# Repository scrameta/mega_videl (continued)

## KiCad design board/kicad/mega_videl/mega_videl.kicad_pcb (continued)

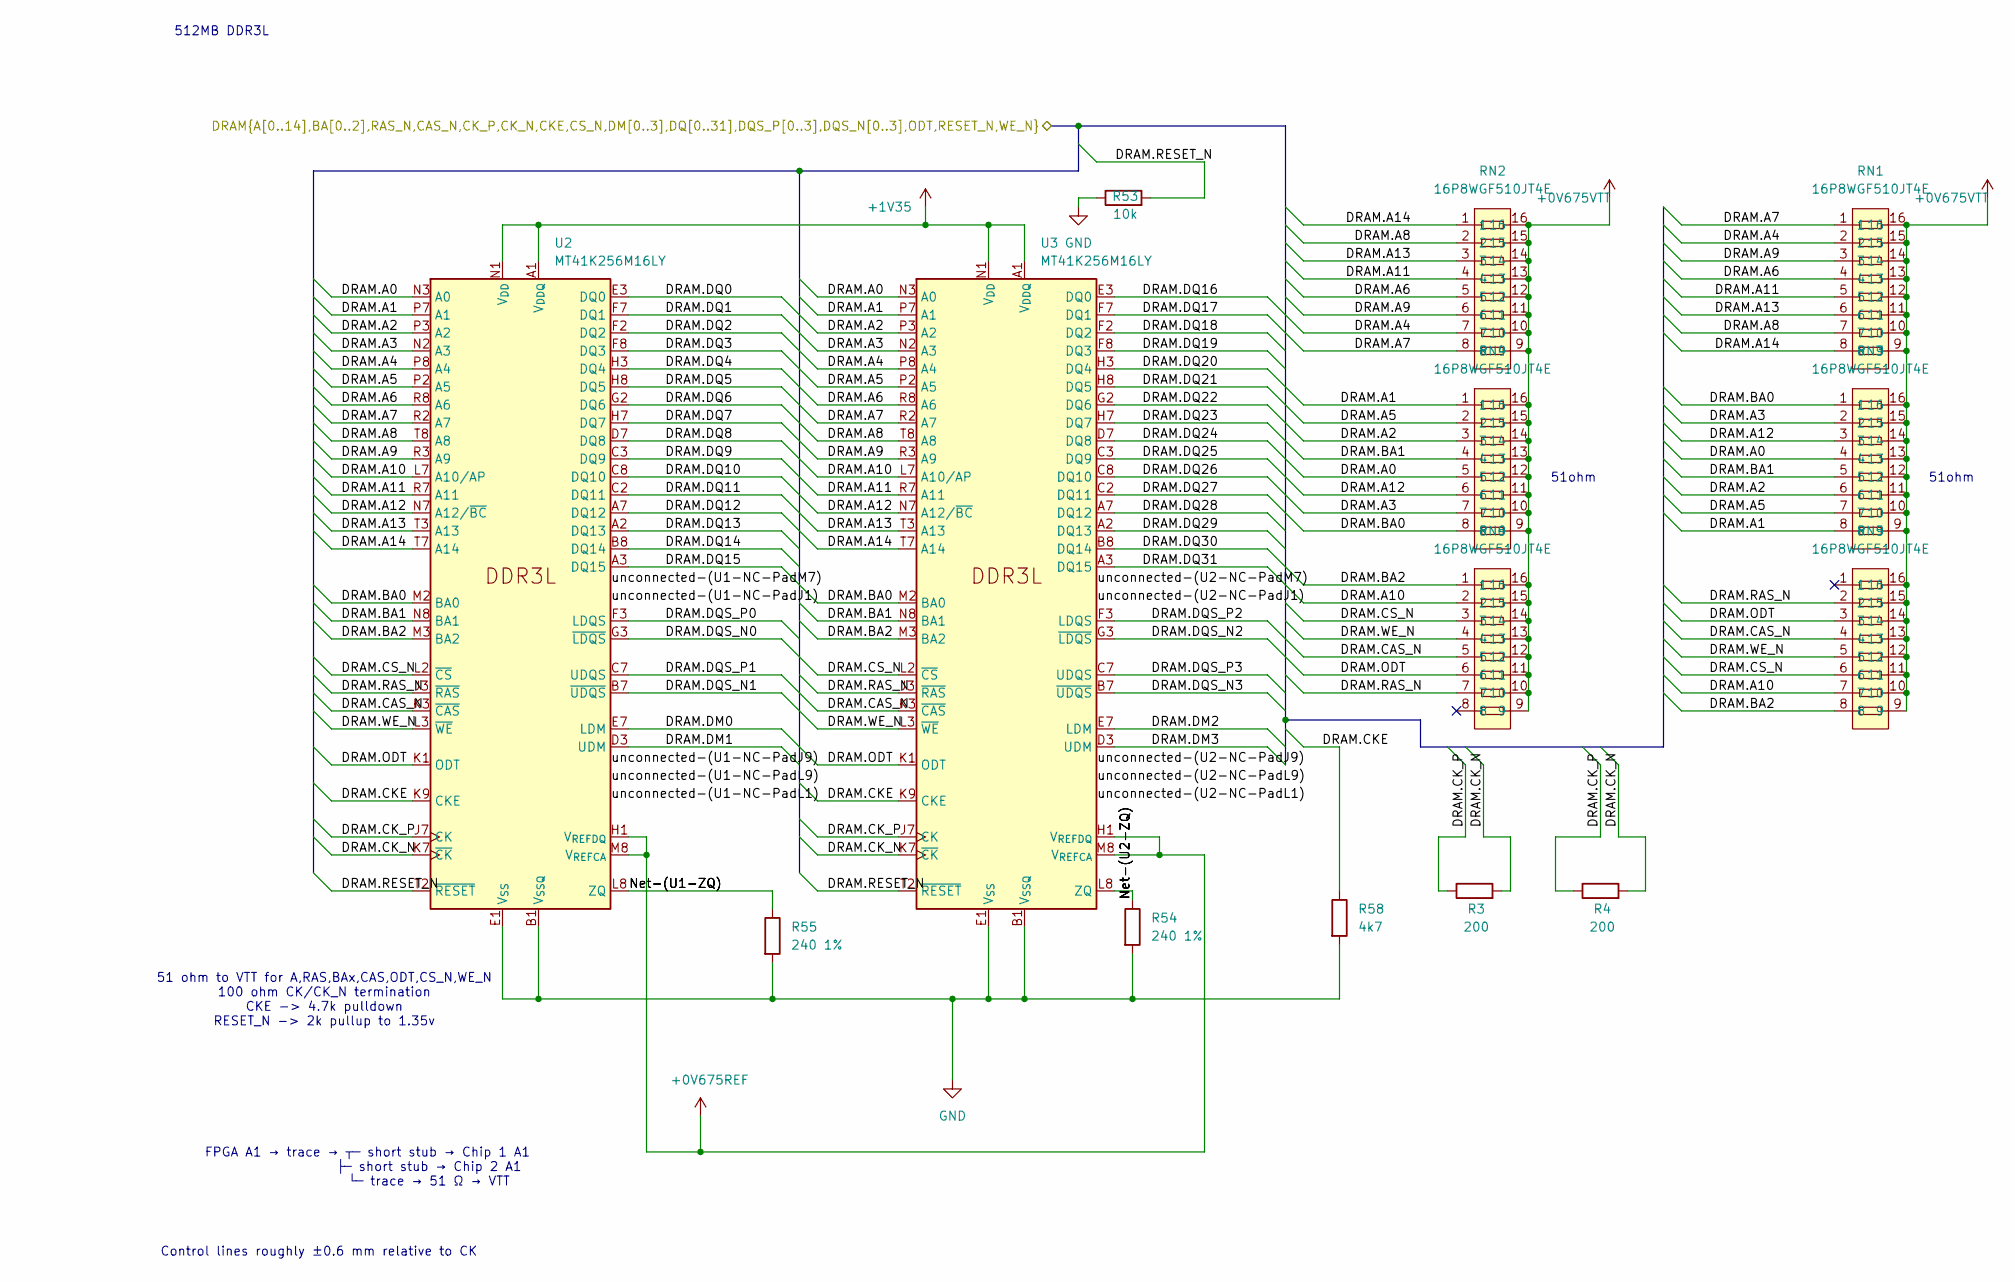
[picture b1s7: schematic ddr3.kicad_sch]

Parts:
R3, R4: 200; R_0402_1005Metric; LCSC C25087
R53: 10k; R_0603_1608Metric; LCSC C25804
R54, R55: 240 1%; R_0603_1608Metric; LCSC C23350
R58: 4k7; R_0603_1608Metric; LCSC C23162
RN1, RN2, RN3, RN4, RN5, RN6: 16P8WGF510JT4E; RES-ARRAY-SMD_0402-16P-L4.0-W1.6-BL-1; MPN 16P8WGF510JT4E; LCSC Part C422180
U2, U3: MT41K256M16LY; FBGA-96_L13.5-W7.5-P0.80-TL_MT41J256M16LY-091G; LCSC Part C253882

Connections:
+0V675REF: U2.H1 (V_{REFDQ}), U2.M8 (V_{REFCA}), U3.H1 (V_{REFDQ}), U3.M8 (V_{REFCA}); also elsewhere on the board
+0V675VTT: RN1.9, RN1.10, RN1.11, RN1.12, RN1.13, RN1.14, RN1.15, RN1.16, RN2.9, RN2.10, RN2.11, RN2.12, RN2.13, RN2.14, RN2.15, RN2.16, RN3.9, RN3.10, RN3.11, RN3.12, RN3.13, RN3.14, RN3.15, RN3.16, RN4.9, RN4.10, RN4.11, RN4.12, RN4.13, RN4.14, RN4.15, RN4.16, RN5.9, RN5.10, RN5.11, RN5.12, RN5.13, RN5.14, RN5.15, RN5.16, RN6.9, RN6.10, RN6.11, RN6.12, RN6.13, RN6.14, RN6.15, RN6.16; also elsewhere on the board
+1V35: U2.A1 (V_{DDQ}), U2.A8 (V_{DDQ}), U2.B2 (V_{DD}), U2.C1 (V_{DDQ}), U2.C9 (V_{DDQ}), U2.D2 (V_{DDQ}), U2.D9 (V_{DD}), U2.E9 (V_{DDQ}), U2.F1 (V_{DDQ}), U2.G7 (V_{DD}), U2.H2 (V_{DDQ}), U2.H9 (V_{DDQ}), U2.K2 (V_{DD}), U2.K8 (V_{DD}), U2.N1 (V_{DD}), U2.N9 (V_{DD}), U2.R1 (V_{DD}), U2.R9 (V_{DD}), U3.A1 (V_{DDQ}), U3.A8 (V_{DDQ}), U3.B2 (V_{DD}), U3.C1 (V_{DDQ}), U3.C9 (V_{DDQ}), U3.D2 (V_{DDQ}), U3.D9 (V_{DD}), U3.E9 (V_{DDQ}), U3.F1 (V_{DDQ}), U3.G7 (V_{DD}), U3.H2 (V_{DDQ}), U3.H9 (V_{DDQ}), U3.K2 (V_{DD}), U3.K8 (V_{DD}), U3.N1 (V_{DD}), U3.N9 (V_{DD}), U3.R1 (V_{DD}), U3.R9 (V_{DD}); also elsewhere on the board
/ddr3/Net-(U1-ZQ): R55.1, U2.L8 (ZQ)
/ddr3/Net-(U2-ZQ): R54.1, U3.L8 (ZQ)
/fpga/DRAM.A0: RN3.4, RN4.5, U2.N3 (A0), U3.N3 (A0); also elsewhere on the board
/fpga/DRAM.A1: RN3.8, RN4.1, U2.P7 (A1), U3.P7 (A1); also elsewhere on the board
/fpga/DRAM.A2: RN3.6, RN4.3, U2.P3 (A2), U3.P3 (A2); also elsewhere on the board
/fpga/DRAM.A3: RN3.2, RN4.7, U2.N2 (A3), U3.N2 (A3); also elsewhere on the board
/fpga/DRAM.A4: RN1.2, RN2.7, U2.P8 (A4), U3.P8 (A4); also elsewhere on the board
/fpga/DRAM.A5: RN3.7, RN4.2, U2.P2 (A5), U3.P2 (A5); also elsewhere on the board
/fpga/DRAM.A6: RN1.4, RN2.5, U2.R8 (A6), U3.R8 (A6); also elsewhere on the board
/fpga/DRAM.A7: RN1.1, RN2.8, U2.R2 (A7), U3.R2 (A7); also elsewhere on the board
/fpga/DRAM.A8: RN1.7, RN2.2, U2.T8 (A8), U3.T8 (A8); also elsewhere on the board
/fpga/DRAM.A9: RN1.3, RN2.6, U2.R3 (A9), U3.R3 (A9); also elsewhere on the board
/fpga/DRAM.A10: RN5.7, RN6.2, U2.L7 (A10/AP), U3.L7 (A10/AP); also elsewhere on the board
/fpga/DRAM.A11: RN1.5, RN2.4, U2.R7 (A11), U3.R7 (A11); also elsewhere on the board
/fpga/DRAM.A12: RN3.3, RN4.6, U2.N7 (A12/~BC), U3.N7 (A12/~BC); also elsewhere on the board
/fpga/DRAM.A13: RN1.6, RN2.3, U2.T3 (A13), U3.T3 (A13); also elsewhere on the board
/fpga/DRAM.A14: RN1.8, RN2.1, U2.T7 (A14), U3.T7 (A14); also elsewhere on the board
/fpga/DRAM.BA0: RN3.1, RN4.8, U2.M2 (BA0), U3.M2 (BA0); also elsewhere on the board
/fpga/DRAM.BA1: RN3.5, RN4.4, U2.N8 (BA1), U3.N8 (BA1); also elsewhere on the board
/fpga/DRAM.BA2: RN5.8, RN6.1, U2.M3 (BA2), U3.M3 (BA2); also elsewhere on the board
/fpga/DRAM.CAS_N: RN5.4, RN6.5, U2.K3 (~CAS), U3.K3 (~CAS); also elsewhere on the board
/fpga/DRAM.CKE: R58.1, U2.K9 (CKE), U3.K9 (CKE); also elsewhere on the board
/fpga/DRAM.CK_N: R3.2, R4.2, U2.K7 (~CK), U3.K7 (~CK); also elsewhere on the board
/fpga/DRAM.CK_P: R3.1, R4.1, U2.J7 (CK), U3.J7 (CK); also elsewhere on the board
/fpga/DRAM.CS_N: RN5.6, RN6.3, U2.L2 (~CS), U3.L2 (~CS); also elsewhere on the board
/fpga/DRAM.DM0: U2.E7 (LDM); also elsewhere on the board
/fpga/DRAM.DM1: U2.D3 (UDM); also elsewhere on the board
/fpga/DRAM.DM2: U3.E7 (LDM); also elsewhere on the board
/fpga/DRAM.DM3: U3.D3 (UDM); also elsewhere on the board
/fpga/DRAM.DQ0: U2.E3 (DQ0); also elsewhere on the board
/fpga/DRAM.DQ1: U2.F7 (DQ1); also elsewhere on the board
/fpga/DRAM.DQ2: U2.F2 (DQ2); also elsewhere on the board
/fpga/DRAM.DQ3: U2.F8 (DQ3); also elsewhere on the board
/fpga/DRAM.DQ4: U2.H3 (DQ4); also elsewhere on the board
/fpga/DRAM.DQ5: U2.H8 (DQ5); also elsewhere on the board
/fpga/DRAM.DQ6: U2.G2 (DQ6); also elsewhere on the board
/fpga/DRAM.DQ7: U2.H7 (DQ7); also elsewhere on the board
/fpga/DRAM.DQ8: U2.D7 (DQ8); also elsewhere on the board
/fpga/DRAM.DQ9: U2.C3 (DQ9); also elsewhere on the board
/fpga/DRAM.DQ10: U2.C8 (DQ10); also elsewhere on the board
/fpga/DRAM.DQ11: U2.C2 (DQ11); also elsewhere on the board
/fpga/DRAM.DQ12: U2.A7 (DQ12); also elsewhere on the board
/fpga/DRAM.DQ13: U2.A2 (DQ13); also elsewhere on the board
/fpga/DRAM.DQ14: U2.B8 (DQ14); also elsewhere on the board
/fpga/DRAM.DQ15: U2.A3 (DQ15); also elsewhere on the board
/fpga/DRAM.DQ16: U3.E3 (DQ0); also elsewhere on the board
/fpga/DRAM.DQ17: U3.F7 (DQ1); also elsewhere on the board
/fpga/DRAM.DQ18: U3.F2 (DQ2); also elsewhere on the board
/fpga/DRAM.DQ19: U3.F8 (DQ3); also elsewhere on the board
/fpga/DRAM.DQ20: U3.H3 (DQ4); also elsewhere on the board
/fpga/DRAM.DQ21: U3.H8 (DQ5); also elsewhere on the board
/fpga/DRAM.DQ22: U3.G2 (DQ6); also elsewhere on the board
/fpga/DRAM.DQ23: U3.H7 (DQ7); also elsewhere on the board
/fpga/DRAM.DQ24: U3.D7 (DQ8); also elsewhere on the board
/fpga/DRAM.DQ25: U3.C3 (DQ9); also elsewhere on the board
/fpga/DRAM.DQ26: U3.C8 (DQ10); also elsewhere on the board
/fpga/DRAM.DQ27: U3.C2 (DQ11); also elsewhere on the board
/fpga/DRAM.DQ28: U3.A7 (DQ12); also elsewhere on the board
/fpga/DRAM.DQ29: U3.A2 (DQ13); also elsewhere on the board
/fpga/DRAM.DQ30: U3.B8 (DQ14); also elsewhere on the board
/fpga/DRAM.DQ31: U3.A3 (DQ15); also elsewhere on the board
/fpga/DRAM.DQS_N0: U2.G3 (~LDQS); also elsewhere on the board
/fpga/DRAM.DQS_N1: U2.B7 (~UDQS); also elsewhere on the board
/fpga/DRAM.DQS_N2: U3.G3 (~LDQS); also elsewhere on the board
/fpga/DRAM.DQS_N3: U3.B7 (~UDQS); also elsewhere on the board
/fpga/DRAM.DQS_P0: U2.F3 (LDQS); also elsewhere on the board
/fpga/DRAM.DQS_P1: U2.C7 (UDQS); also elsewhere on the board
/fpga/DRAM.DQS_P2: U3.F3 (LDQS); also elsewhere on the board
/fpga/DRAM.DQS_P3: U3.C7 (UDQS); also elsewhere on the board
/fpga/DRAM.ODT: RN5.3, RN6.6, U2.K1 (ODT), U3.K1 (ODT); also elsewhere on the board
/fpga/DRAM.RAS_N: RN5.2, RN6.7, U2.J3 (~RAS), U3.J3 (~RAS); also elsewhere on the board
/fpga/DRAM.RESET_N: R53.2, U2.T2 (~RESET), U3.T2 (~RESET); also elsewhere on the board
/fpga/DRAM.WE_N: RN5.5, RN6.4, U2.L3 (~WE), U3.L3 (~WE); also elsewhere on the board
GND: R53.1, R54.2, R55.2, R58.2, U2.A9 (V_{SS}), U2.B1 (V_{SSQ}), U2.B3 (V_{SS}), U2.B9 (V_{SSQ}), U2.D1 (V_{SSQ}), U2.D8 (V_{SSQ}), U2.E1 (V_{SS}), U2.E2 (V_{SSQ}), U2.E8 (V_{SSQ}), U2.F9 (V_{SSQ}), U2.G1 (V_{SSQ}), U2.G8 (V_{SS}), U2.G9 (V_{SSQ}), U2.J2 (V_{SS}), U2.J8 (V_{SS}), U2.M1 (V_{SS}), U2.M9 (V_{SS}), U2.P1 (V_{SS}), U2.P9 (V_{SS}), U2.T1 (V_{SS}), U2.T9 (V_{SS}), U3.A9 (V_{SS}), U3.B1 (V_{SSQ}), U3.B3 (V_{SS}), U3.B9 (V_{SSQ}), U3.D1 (V_{SSQ}), U3.D8 (V_{SSQ}), U3.E1 (V_{SS}), U3.E2 (V_{SSQ}), U3.E8 (V_{SSQ}), U3.F9 (V_{SSQ}), U3.G1 (V_{SSQ}), U3.G8 (V_{SS}), U3.G9 (V_{SSQ}), U3.J2 (V_{SS}), U3.J8 (V_{SS}), U3.M1 (V_{SS}), U3.M9 (V_{SS}), U3.P1 (V_{SS}), U3.P9 (V_{SS}), U3.T1 (V_{SS}), U3.T9 (V_{SS}); also elsewhere on the board

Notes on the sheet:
51ohm
512MB DDR3L
Control lines roughly ±0.6 mm relative to CK
FPGA A1 → trace → ┬─ short stub → Chip 1 A1 ├─ short stub → Chip 2 A1 └─ trace → 51 Ω → VTT
51 ohm to VTT for A,RAS,BAx,CAS,ODT,CS_N,WE_N 100 ohm CK/CK_N termination CKE -> 4.7k pulldown RESET_N -> 2k pullup to 1.35v

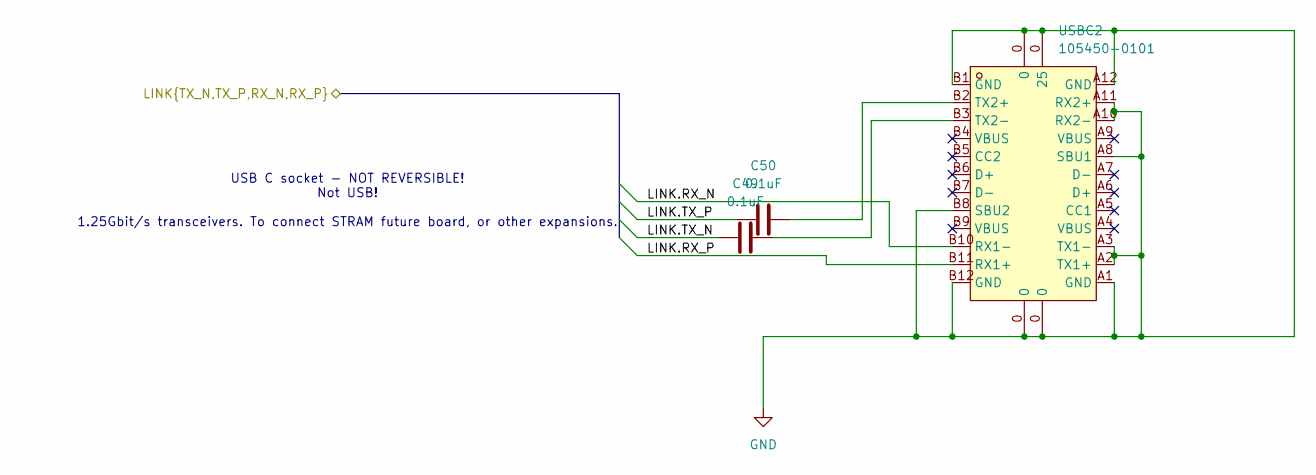
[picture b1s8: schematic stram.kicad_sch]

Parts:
C49, C50: 0.1uF; C_0603_1608Metric; LCSC C14663
USBC2: 105450-0101; USB-C-SMD_TYPE-C-USB-18; MPN 1054500101; LCSC Part C134092

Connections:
/fpga/LINK.RX_N: USBC2.B10 (RX1-); also elsewhere on the board
/fpga/LINK.RX_P: USBC2.B11 (RX1+); also elsewhere on the board
/fpga/LINK.TX_N: C49.1; also elsewhere on the board
/fpga/LINK.TX_P: C50.1; also elsewhere on the board
GND: USBC2.0, USBC2.A1 (GND), USBC2.A2 (TX1+), USBC2.A3 (TX1-), USBC2.A8 (SBU1), USBC2.A10 (RX2-), USBC2.A11 (RX2+), USBC2.A12 (GND), USBC2.B1 (GND), USBC2.B8 (SBU2), USBC2.B12 (GND); also elsewhere on the board
unnamed: C50.2, USBC2.B2 (TX2+)
unnamed: C49.2, USBC2.B3 (TX2-)

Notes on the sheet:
USB C socket - NOT REVERSIBLE! Not USB! 1.25Gbit/s transceivers. To connect STRAM future board, or other expansions.

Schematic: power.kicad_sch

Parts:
C13: 100uF; C_1206_3216Metric; LCSC C7432784
C16, C22: 10nF; C_0402_1005Metric; LCSC C15195
C19, C23, C25: 10uF; C_0805_2012Metric; LCSC C15850
C21, C24, C27: 22uF; C_0805_2012Metric; LCSC C45783
J2: Conn_01x04; PinHeader_1x04_P2.54mm_Vertical; not fitted
L1, L2: 1uF/DFE252012F-1R0M=P2; L_1008_2520Metric; LCSC C435392
R5: 11K0; R_0603_1608Metric; LCSC C25950
R6, R14: 32k4; R_0603_1608Metric; LCSC C13187
R7, R15: 10k; R_0603_1608Metric; LCSC C25804
R13: 16K9; R_0603_1608Metric; LCSC C25954
U4, U8: TPS62903RPJR; VQFN-HR-9_L2.0-W1.5-P0.50-TL; Manufacturer Part TPS62903RPJR; LCSC C2866502
U6: TPS7A2025PDBVR; SOT-23-5_L2.9-W1.6-P0.95-LS2.8-BR; MPN TPS7A2025PDBVR; LCSC Part C2869949

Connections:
+1V1: C21.1, J2.4, L1.1, U4.3 (VOS); also elsewhere on the board
+1V35: C27.1, J2.3, L2.1, U8.3 (VOS); also elsewhere on the board
+2V5: C24.1, U6.5 (OUT); also elsewhere on the board
+3V3: C13.1, C19.1, C23.1, C25.1, J2.2, R7.1, R15.1, U4.5 (EN), U4.6 (VIN), U6.1 (IN), U6.3 (EN), U8.5 (EN), U8.6 (VIN); also elsewhere on the board
/power/Net-(U15-FB/VSET): R5.1, U4.9 (FB/VSET)
/power/Net-(U15-MODE/S-CONF): R6.1, U4.7 (MODE/S-CONF)
/power/Net-(U15-PG): R7.2, U4.1 (PG)
/power/Net-(U15-SS/TR): C16.1, U4.8 (SS/TR)
/power/Net-(U15-SW): L1.2, U4.2 (SW)
/power/Net-(U16-FB/VSET): R13.1, U8.9 (FB/VSET)
/power/Net-(U16-MODE/S-CONF): R14.1, U8.7 (MODE/S-CONF)
/power/Net-(U16-PG): R15.2, U8.1 (PG)
/power/Net-(U16-SS/TR): C22.1, U8.8 (SS/TR)
/power/Net-(U16-SW): L2.2, U8.2 (SW)
/power/unconnected-(U8-N/C-Pad4): U6.4 (N/C)
GND: C13.2, C16.2, C19.2, C21.2, C22.2, C23.2, C24.2, C25.2, C27.2, J2.1, R5.2, R6.2, R13.2, R14.2, U4.4 (GND), U6.2 (GND), U8.4 (GND); also elsewhere on the board

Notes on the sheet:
3.3v in from CT60 2.5v LDO (small one from Pokeymax) 1.35v for DDR3L 1.1v for Cyclone VE
Cyclone V G unsequenced -> 1.1(CORE)->2.5(PLL)->1.35(IO) + 3.3 (IO)
MODE VSET 2.5MHz Discharge AUTO = 26.1k to GND VSET 2.5MHz Discharge PWM = 32.4k to GND
VSET 1.35V - 16.9K 1.1V - 11.0K

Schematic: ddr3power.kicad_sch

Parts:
C1, C60, C61: 0.1uF; C_0603_1608Metric; LCSC C14663
C2, C3, C5, C6, C7, C11, C12: 10uF; C_0805_2012Metric; LCSC C15850
C4, C51, C52, C53, C54, C73, C74, C75, C76: 4.7uF; C_0805_2012Metric; LCSC C1779
C8, C9, C14, C15, C17, C18: CA0612KRX7R7BB104; CAP-ARRAY-SMD_0612-8P-L3.2-W1.6-BL; MPN CA0612KRX7R7BB104; LCSC Part C576639
C10: 1nF; C_0603_1608Metric; LCSC C1588
C55, C56, C57, C58, C59, C62, C63, C64, C65, C66, C67, C68, C69, C70, C71, C72: 0.1uF; C_0402_1005Metric; LCSC C1525
R1, R2: 10k; R_0603_1608Metric; LCSC C25804
U1: TPS51200DRCR; WSON-10_L3.0-W3.0-P0.50-BL-EP; MPN TPS51200DRCR; LCSC Part C34771

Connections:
+0V675REF: C1.1, C60.1, C61.1, U1.6 (REFOUT); also elsewhere on the board
+0V675VTT: C2.1, C3.1, C5.1, C6.1, C7.1, C8.5, C8.6, C8.7, C8.8, C9.5, C9.6, C9.7, C9.8, C14.5, C14.6, C14.7, C14.8, C15.5, C15.6, C15.7, C15.8, C17.5, C17.6, C17.7, C17.8, C18.5, C18.6, C18.7, C18.8, U1.3 (VO), U1.5 (VOSNS); also elsewhere on the board
+1V35: C11.1, C12.1, C51.1, C52.1, C53.1, C54.1, C55.1, C56.1, C57.1, C58.1, C59.1, C62.1, C63.1, C64.1, C65.1, C66.1, C67.1, C68.1, C69.1, C70.1, C71.1, C72.1, C73.1, C74.1, C75.1, C76.1, R2.1, U1.2 (VLDOIN); also elsewhere on the board
+3V3: C4.1, U1.7 (EN), U1.10 (VIN); also elsewhere on the board
/ddr3power/Net-(U7-REFIN): C10.1, R1.1, R2.2, U1.1 (REFIN)
/ddr3power/unconnected-(U7-PGOOD-Pad9): U1.9 (PGOOD)
GND: C1.2, C2.2, C3.2, C4.2, C5.2, C6.2, C7.2, C8.1, C8.2, C8.3, C8.4, C9.1, C9.2, C9.3, C9.4, C10.2, C11.2, C12.2, C14.1, C14.2, C14.3, C14.4, C15.1, C15.2, C15.3, C15.4, C17.1, C17.2, C17.3, C17.4, C18.1, C18.2, C18.3, C18.4, C51.2, C52.2, C53.2, C54.2, C55.2, C56.2, C57.2, C58.2, C59.2, C60.2, C61.2, C62.2, C63.2, C64.2, C65.2, C66.2, C67.2, C68.2, C69.2, C70.2, C71.2, C72.2, C73.2, C74.2, C75.2, C76.2, R1.2, U1.4 (PGND), U1.8 (GND), U1.11 (EPAD); also elsewhere on the board

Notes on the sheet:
0.1uF

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
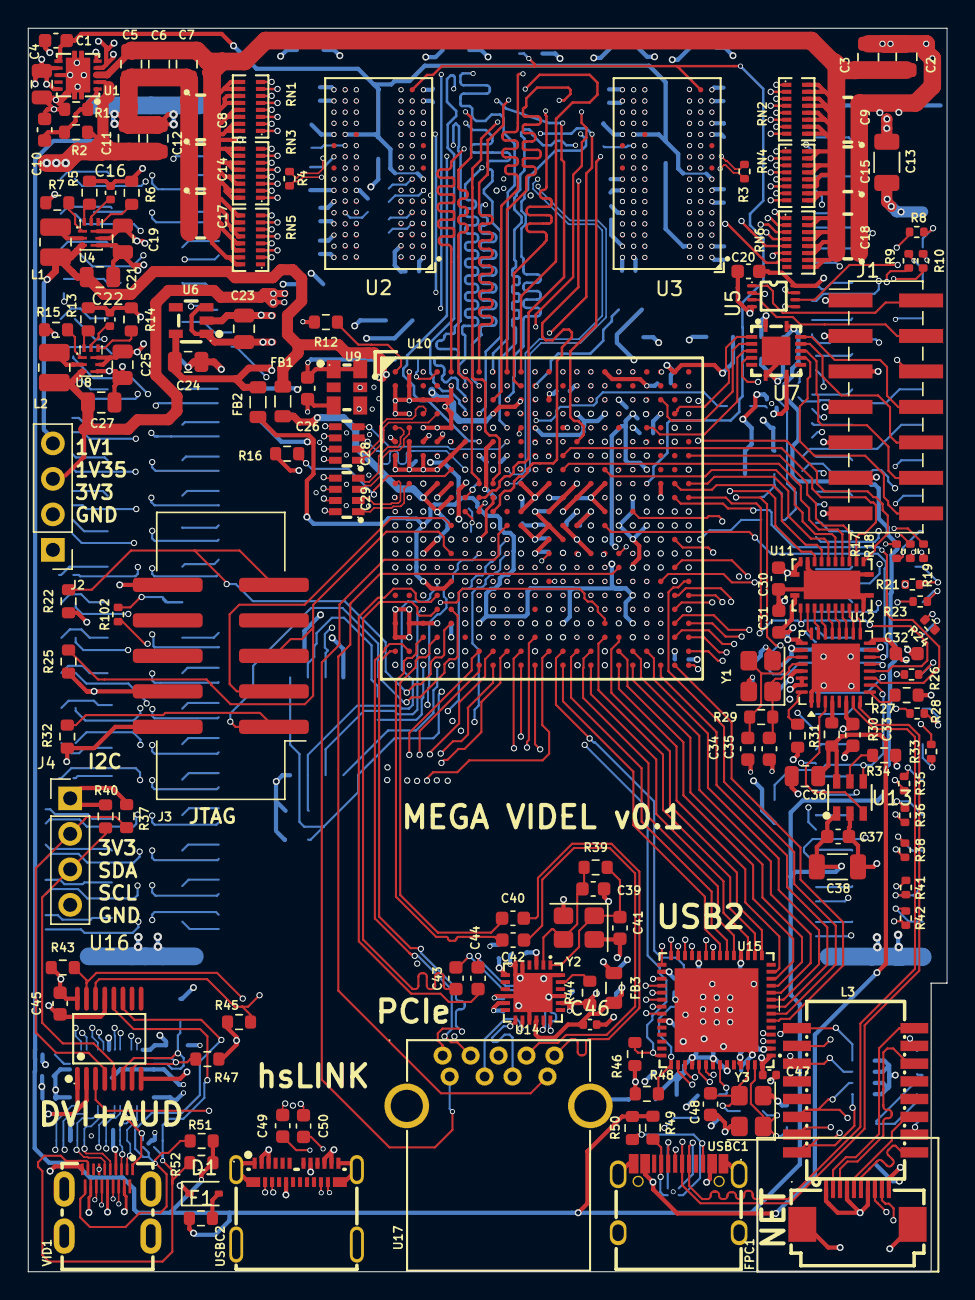
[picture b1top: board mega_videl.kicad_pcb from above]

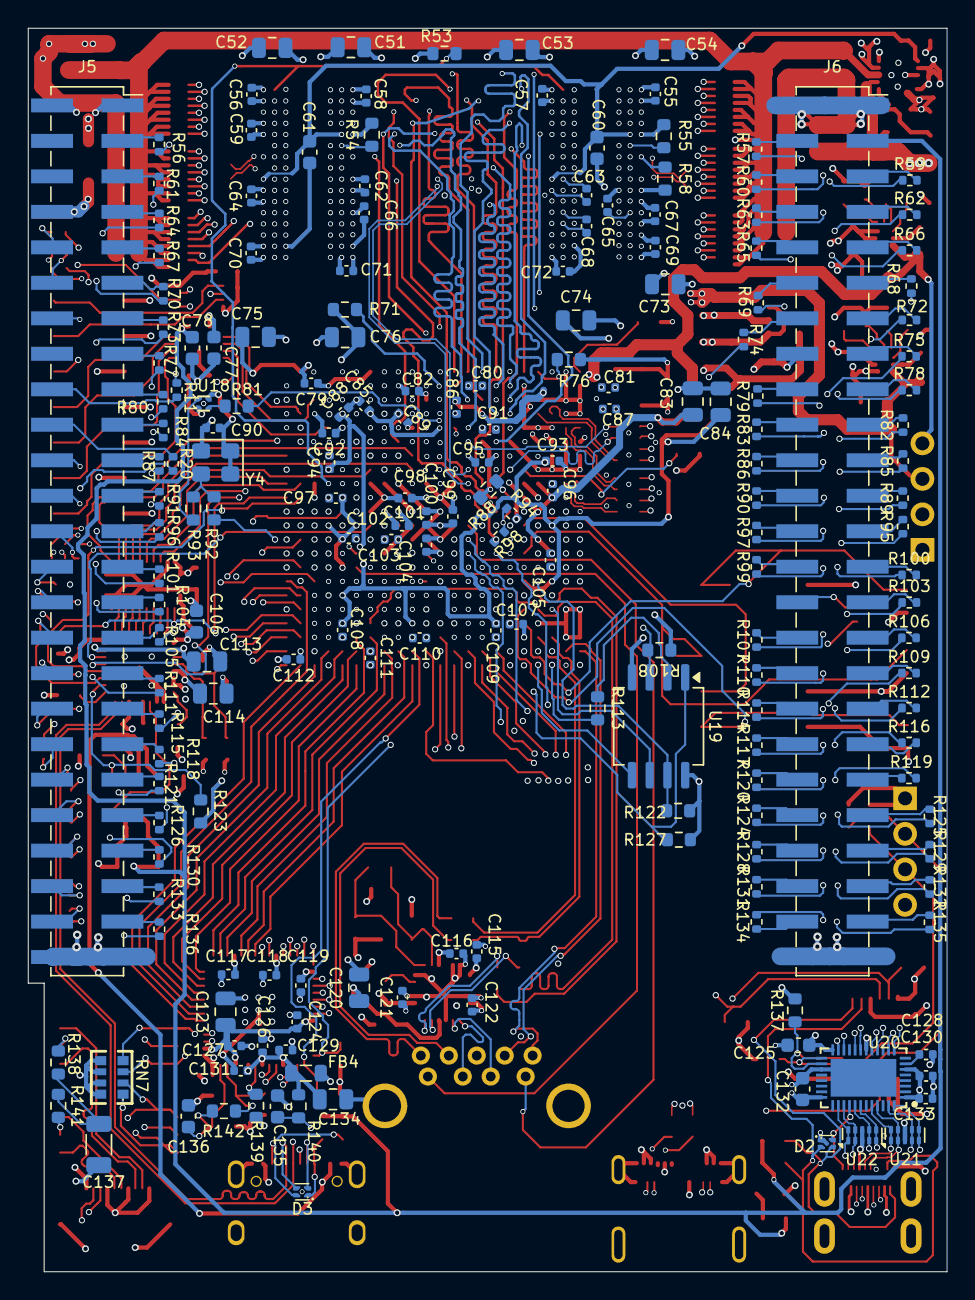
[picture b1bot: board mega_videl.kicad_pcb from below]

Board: 10 copper layers, 65.8 x 89.0 mm, 333 parts (190 on the bottom side), 450 nets.

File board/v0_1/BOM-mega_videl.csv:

Comment,Designator,Footprint,LCSC,Quantity
0,R94,R_0402_1005Metric,C17168,1
0.1uF,"C1,C106,C125,C128,C130,C132,C133,C20,C26,C30,C31,C32,C33,C37,C40,C42,C43,C44,C45,C49,C50,C60,C61,C77,C78",C_0603_1608Metric,C14663,25
0.1uF,"C100,C101,C102,C103,C104,C105,C107,C108,C109,C110,C111,C112,C115,C116,C117,C118,C119,C121,C122,C126,C129,C131,C46,C47,C55,C56,C57,C58,C59,C62,C63,C64,C65,C66,C67,C68,C69,C70,C71,C72,C79,C80,C81,C82,C85,C86,C87,C88,C89,C91,C92,C93,C94,C95,C96,C97,C98,C99",C_0402_1005Metric,C1525,58
10,R140,R_0603_1608Metric,C22859,1
1000pF 2KV,C137,C_1206_3216Metric,C9196,1
100uF,"C13,C38",C_1206_3216Metric,C7432784,2
105450-0101,USBC2,USB-C-SMD_TYPE-C-USB-18,C134092,1
10k,"R1,R108,R122,R123,R127,R15,R16,R2,R22,R25,R53,R7,R76,R88",R_0603_1608Metric,C25804,14
10nF,"C124,C127,C16,C22,C90",C_0402_1005Metric,C15195,5
10uF,"C11,C12,C19,C2,C23,C25,C3,C36,C5,C6,C7",C_0805_2012Metric,C15850,11
11K0,R5,R_0603_1608Metric,C25950,1
12K 1%,R31,R_0603_1608Metric,C22790,1
12k4,R139,R_0603_1608Metric,C137798,1
16K9,R13,R_0603_1608Metric,C25954,1
16P8WGF510JT4E,"RN1,RN2,RN3,RN4,RN5,RN6",RES-ARRAY-SMD_0402-16P-L4.0-W1.6-BL-1,C422180,6
1M,"R142,R29,R39",R_0603_1608Metric,C22935,3
1k,R32,R_0603_1608Metric,C21190,1
1nF,C10,C_0603_1608Metric,C1588,1
1uF/DFE252012F-1R0M=P2,"L1,L2",L_1008_2520Metric,C435392,2
200,"R3,R4",R_0402_1005Metric,C25087,2
20k,R34,R_0603_1608Metric,C4184,1
22,"R113,R81,R92,R93",R_0603_1608Metric,C23345,4
22nF,C135,C_0603_1608Metric,C21122,1
22uF,"C21,C24,C27",C_0805_2012Metric,C45783,3
240 1%,"R54,R55,R71",R_0603_1608Metric,C23350,3
24MHz,Y1,Crystal_SMD_3225-4Pin_3.2x2.5mm,C5308006,1
25MHz,Y3,Crystal_SMD_3225-4Pin_3.2x2.5mm,C5308007,1
25MHz,Y2,Crystal_SMD_3225-4Pin_3.2x2.5mm,C5742221,1
2k,R12,R_0603_1608Metric,C22975,1
30pF,"C136,C34,C35,C48",C_0603_1608Metric,C1658,4
32k4,"R14,R6",R_0603_1608Metric,C13187,2
33,"R10,R100,R101,R102,R103,R104,R105,R106,R107,R109,R11,R110,R111,R112,R114,R115,R116,R117,R118,R119,R120,R121,R124,R125,R126,R128,R129,R130,R131,R132,R133,R134,R135,R136,R17,R18,R19,R20,R21,R23,R24,R26,R28,R33,R35,R36,R38,R41,R42,R56,R57,R59,R60,R61,R62,R63,R64,R65,R66,R67,R68,R69,R70,R72,R73,R74,R75,R77,R78,R79,R8,R80,R82,R83,R84,R85,R86,R87,R89,R9,R90,R91,R95,R96,R97,R99",R_0402_1005Metric,C25105,86
4.7uF,"C113,C114,C120,C123,C134,C4,C51,C52,C53,C54,C73,C74,C75,C76,C83,C84",C_0805_2012Metric,C1779,16
4D03WGF499JT5E,RN7,RES-ARRAY-SMD_0603-8P-L3.2-W1.6-BL,C54832,1
4k7,"R137,R37,R40,R43,R45,R46,R47,R48,R51,R52,R58",R_0603_1608Metric,C23162,11
56K 1%,"R49,R50",R_0603_1608Metric,C23206,2
5CGXFC5C6F23I7N,U10,FBGA-484_L23.0-W23.0-R22-C22-P1.00-TL,C1550726,1
70@100MHz,"FB1,FB2,FB3,FB4",L_0805_2012Metric,C85840,4
74.25MHz,U9,OSC-SMD_6P-L3.2-W2.5-BL_RENESAS_XLH3XXXXXXXXXX,C836732,1
75,"R138,R141",R_0603_1608Metric,C4275,2
820,R30,R_0603_1608Metric,C23253,1
8pF,"C39,C41",C_0603_1608Metric,C327316,2
AP2553AW6-7,U13,SOT-26_L3.0-W1.6-P0.95-LS2.8-BL,C441827,1
ASE-50MHz,Y4,Oscillator_SMD_Abracon_ASE-4Pin_3.2x2.5mm,C5203552,1
CA0612KRX7R7BB104,"C14,C15,C17,C18,C28,C29,C8,C9",CAP-ARRAY-SMD_0612-8P-L3.2-W1.6-BL,C576639,8
CDCBT1001DPWR,U18,X2SON-5_L0.8-W0.8-P0.48-BR,C5215096,1
Conn_02x07_Odd_Even,J1,PinHeader_2x07_P2.54mm_Vertical_SMD,C3975152,1
Conn_02x25_Odd_Even,"J5,J6",PinSocket_2x25_P2.54mm_Vertical_SMD,C52611,2
FPGA JTAG,J3,IDC-Header_2x05_P2.54mm_Vertical_SMD,C2884455,1
H1102N,L3,XFMR-SMD_H1102N,C42418465,1
HC-USB3.0-L168-WP,U17,USB-TH_USB3.0-A,C7501850,1
HDMI-101S,VID1,HDMI-SMD_HDMI-101S,C720620,1
LAN9220-ABZJ,U15,QFN-56_L8.0-W8.0-P0.50-BL-EP6.0,C1521597,1
MT41K256M16LY,"U2,U3",FBGA-96_L13.5-W7.5-P0.80-TL_MT41J256M16LY-091G,C253882,2
N25Q/MT25Q,U19,SOIC-8_5.3x6.2mm_P1.27mm,C2802705,1
PCA9546APWR,U16,TSSOP-16_L5.0-W4.4-P0.65-LS6.4-BL,C400705,1
PI6CG33201CZDIEX,U14,TQFN-24_L4.0-W4.0-P0.50-TL-EP2.8,C1236517,1
PMEG - 0.25v drop,D1,D_SOD-323,C7420331,1
Polyfuse 0.2A,F1,R_0603_1608Metric,C207011,1
SN74LVC3G34DCUR,U5,VSSOP-8_L2.1-W2.4-P0.50-LS3.2-BR,C130024,1
TMDS1204IRNQR,U20,WQFN-40_L6.0-W4.0-P0.40-TL-EP4.7,C19272424,1
TPD4E02B04DQA,"U21,U22",USON-10_2.5x1.0mm_P0.5mm,C106794,2
TPD4E6B06DPWR,"D2,D3",X2SON-4_L0.8-W0.8-P0.48-TL-A,C2869397,2
TPS51200DRCR,U1,WSON-10_L3.0-W3.0-P0.50-BL-EP,C34771,1
TPS62903RPJR,"U4,U8",VQFN-HR-9_L2.0-W1.5-P0.50-TL,C2866502,2
TPS7A2025PDBVR,U6,SOT-23-5_L2.9-W1.6-P0.95-LS2.8-BR,C2869949,1
TXB0104RGYR,U7,VQFN-14_L3.5-W3.5-P0.50-BL-EP,C400708,1
TXV0108RGYR,U11,TQFN-24_L5.5-W3.5-P0.50-BR-EP,C22428389,1
TYPE-C-31-M-12,USBC1,USB-C_SMD-TYPE-C-31-M-12_1,C165948,1
USB3300-EZK,U12,QFN-32-1EP_5x5mm_P0.5mm_EP3.45x3.45mm,C108383,1
X05A20L10T,FPC1,FFC-SMD_10P-P0.50_X05A20L10T,C388667,1
